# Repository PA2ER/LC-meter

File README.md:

# LC-meter
## Description
induction and capacity meter with pic controller.
*  Work in progress!!!
*  Finished version V1.0 of the PCB.
 
 Back side of the PCB.
 
 Front side of the PCB.
## Schematics
  
<!--stackedit_data:
eyJoaXN0b3J5IjpbLTg0MDYxMjgyM119
-->

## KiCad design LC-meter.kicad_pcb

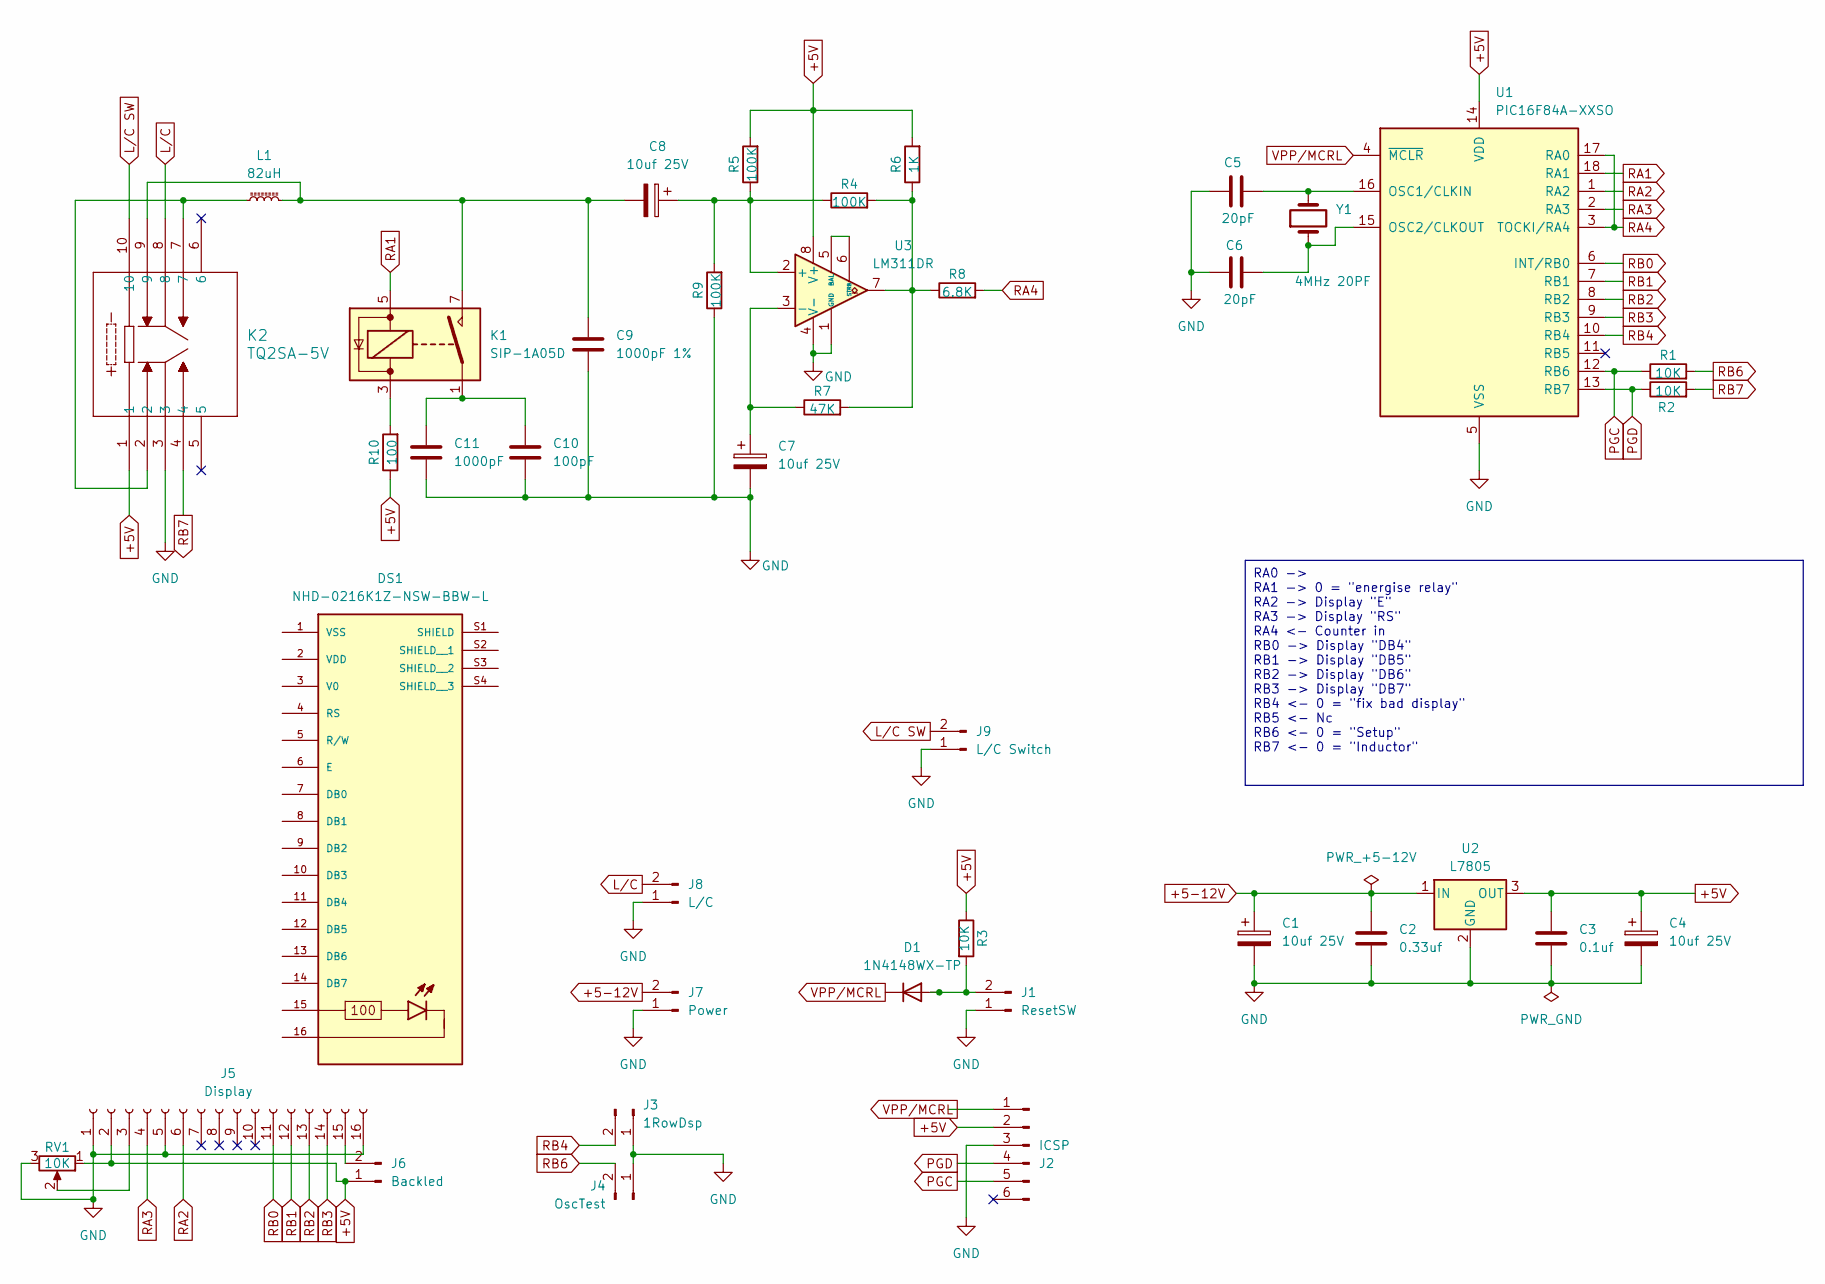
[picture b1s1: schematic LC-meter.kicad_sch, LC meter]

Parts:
C1, C4, C7, C8: 10uf 25V; CP_EIA-6032-28_Kemet-C_Pad2.25x2.35mm_HandSolder; Digikey 293D106X0025C2TE3
C2: 0.33uf; C_0805_2012Metric_Pad1.18x1.45mm_HandSolder; Digikey CC0805KKX7R8BB334
C3: 0.1uf; C_0805_2012Metric_Pad1.18x1.45mm_HandSolder; Digikey CC0805KRX7R9BB104
C5, C6: 20pF; C_0805_2012Metric_Pad1.18x1.45mm_HandSolder; Digikey C0805C200J5HAC7800
C9: 1000pF 1%; C_0805_2012Metric_Pad1.18x1.45mm_HandSolder; Digikey CC0805FRNPO9BN102
C10: 100pF; C_0805_2012Metric_Pad1.18x1.45mm_HandSolder; Digikey CC0805FRNPO9BN101
C11: 1000pF; C_0805_2012Metric_Pad1.18x1.45mm_HandSolder; Digikey CC0805FRNPO9BN102
D1: 1N4148WX-TP; D_SOD-323_HandSoldering; Digikey 1N4148WX-TP
DS1: NHD-0216K1Z-NSW-BBW-L; NHD_NHD-0216K1Z-NSW-BBW-L; PARTREV 03/28/17
J1: ResetSW; PinHeader_1x02_P2.54mm_Vertical
J2: ICSP; PinHeader_1x06_P2.54mm_Vertical
J3: 1RowDsp; PinHeader_1x02_P2.54mm_Vertical
J4: OscTest; PinHeader_1x02_P2.54mm_Vertical
J5: Display; PinHeader_1x16_P2.54mm_Vertical
J6: Backled; PinHeader_1x02_P2.54mm_Vertical
J7: Power; PinHeader_1x02_P2.54mm_Vertical
J8: L/C; PinHeader_1x02_P2.54mm_Vertical
J9: L/C Switch; PinHeader_1x02_P2.54mm_Vertical
K1: SIP-1A05D; Relay_SPST_StandexMeder_MS_Form1AB; Digikey SIP-1A05D
K2: TQ2SA-5V; RELAY_TQ2_SA_PAN-L
L1: 82uH; L_1210_3225Metric_Pad1.42x2.65mm_HandSolder; Digikey NLV32T-820J-EF
R1, R2, R3: 10K; R_0805_2012Metric_Pad1.20x1.40mm_HandSolder
R4, R5, R9: 100K; R_0805_2012Metric_Pad1.20x1.40mm_HandSolder
R6: 1K; R_0805_2012Metric_Pad1.20x1.40mm_HandSolder
R7: 47K; R_0805_2012Metric_Pad1.20x1.40mm_HandSolder
R8: 6.8K; R_0805_2012Metric_Pad1.20x1.40mm_HandSolder
R10: 100; R_0805_2012Metric_Pad1.20x1.40mm_HandSolder
RV1: 10K; Potentiometer_Bourns_TC33X_Vertical; Digikey TC33X-2-103E
U1: PIC16F84A-XXSO; SOIC-18W_7.5x11.6mm_P1.27mm; Digikey PIC16F84A-04/SO-ND
U2: L7805; TO-252-3_TabPin2; Digikey AS7805ADTR-G1DI
U3: LM311DR; SOIC-8_3.9x4.9mm_P1.27mm; Digikey IC COMPARATOR 1 GEN PUR 8SOIC
Y1: 4MHz 20PF; Crystal_SMD_HC49-SD_HandSoldering; Digikey 4M20P2/49SMT

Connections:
+5-12V: C1.1, C2.1, J7.2, U2.1 (IN)
+5V: C3.1, C4.1, J2.2, J5.2, J6.1, K2.1, R3.1, R5.2, R6.2, R10.1, RV1.1, U1.14 (VDD), U2.3 (OUT), U3.8 (V+)
GND: C1.2, C2.2, C3.2, C4.2, C5.1, C6.1, C7.2, C9.2, C10.2, C11.2, J1.1, J2.3, J3.1, J4.1, J5.1, J5.5, J5.16, J7.1, J8.1, J9.1, K2.3, R9.1, RV1.3, U1.5 (VSS), U2.2 (GND), U3.1 (GND), U3.4 (V-)
L/C: J8.2, K2.8
L/C SW: J9.2, K2.10
unnamed: C8.2, C9.1, K1.7, K2.9, L1.2
unnamed: C10.1, C11.1, K1.1
unnamed: D1.2 (A), J1.2, R3.2
unnamed: J5.3, RV1.2
unnamed: J5.15, J6.2
unnamed: K1.3, R10.2
unnamed: K2.2, K2.7, L1.1
unnamed: R4.2, R6.1, R7.2, R8.1, U3.7
unnamed: C5.2, U1.16 (OSC1/CLKIN), Y1.2
unnamed: C6.2, U1.15 (OSC2/CLKOUT), Y1.1
unnamed: C8.1, R4.1, R5.1, R9.2, U3.2 (+)
unnamed: C7.1, R7.1, U3.3 (-)
unnamed: U3.5 (BAL), U3.6 (STRB)
PGC: J2.5, R1.1, U1.12 (RB6)
PGD: J2.4, R2.1, U1.13 (RB7)
RA1: K1.5, U1.18 (RA1)
RA2: J5.6, U1.1 (RA2)
RA3: J5.4, U1.2 (RA3)
RA4: R8.2, U1.3 (TOCKI/RA4), U1.17 (RA0)
RB0: J5.11, U1.6 (INT/RB0)
RB1: J5.12, U1.7 (RB1)
RB2: J5.13, U1.8 (RB2)
RB3: J5.14, U1.9 (RB3)
RB4: J3.2, U1.10 (RB4)
RB6: J4.2, R1.2
RB7: K2.4, R2.2
VPP/MCRL: D1.1 (K), J2.1, U1.4 (~MCLR)

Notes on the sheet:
RA0 -> RA1 -> 0 = "energise relay" RA2 -> Display "E" RA3 -> Display "RS" RA4 <- Counter in RB0 -> Display "DB4" RB1 -> Display "DB5" RB2 -> Display "DB6" RB3 -> Display "DB7" RB4 <- 0 = "fix bad display" RB5 <- Nc RB6 <- 0 = "Setup" RB7 <- 0 = "Inductor"

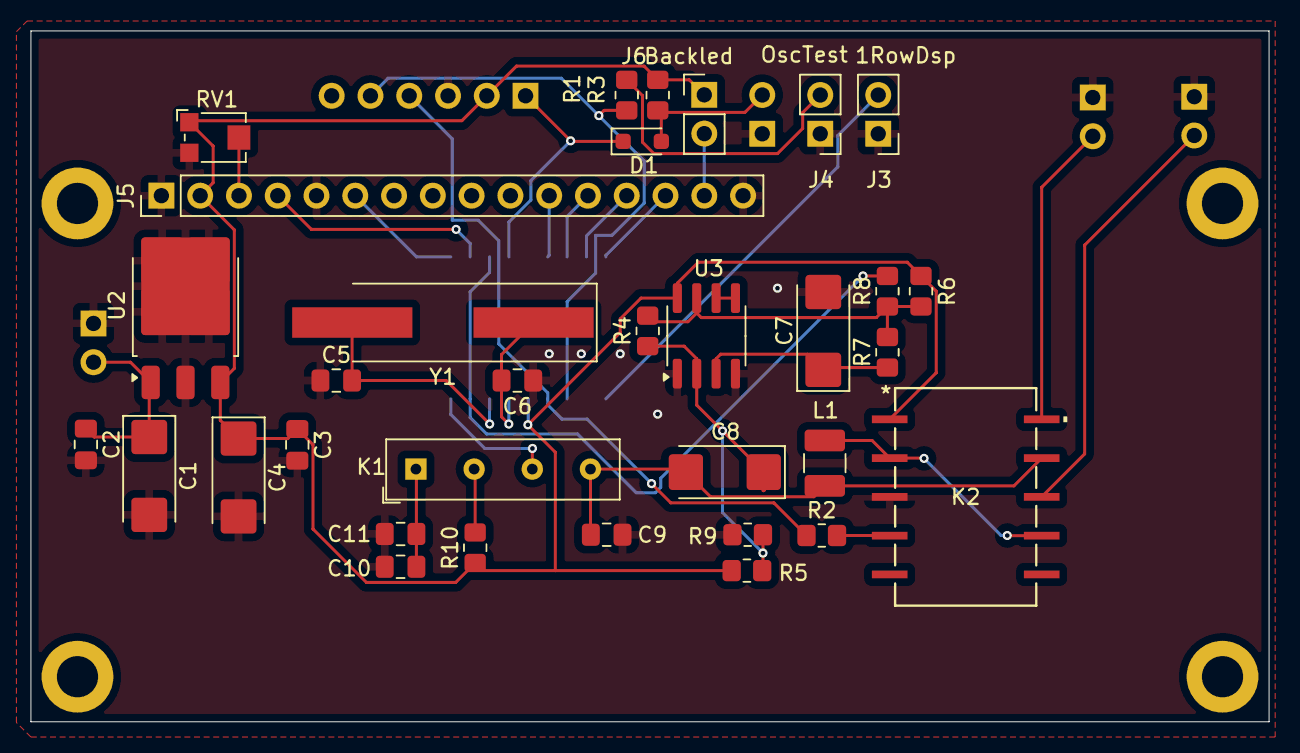
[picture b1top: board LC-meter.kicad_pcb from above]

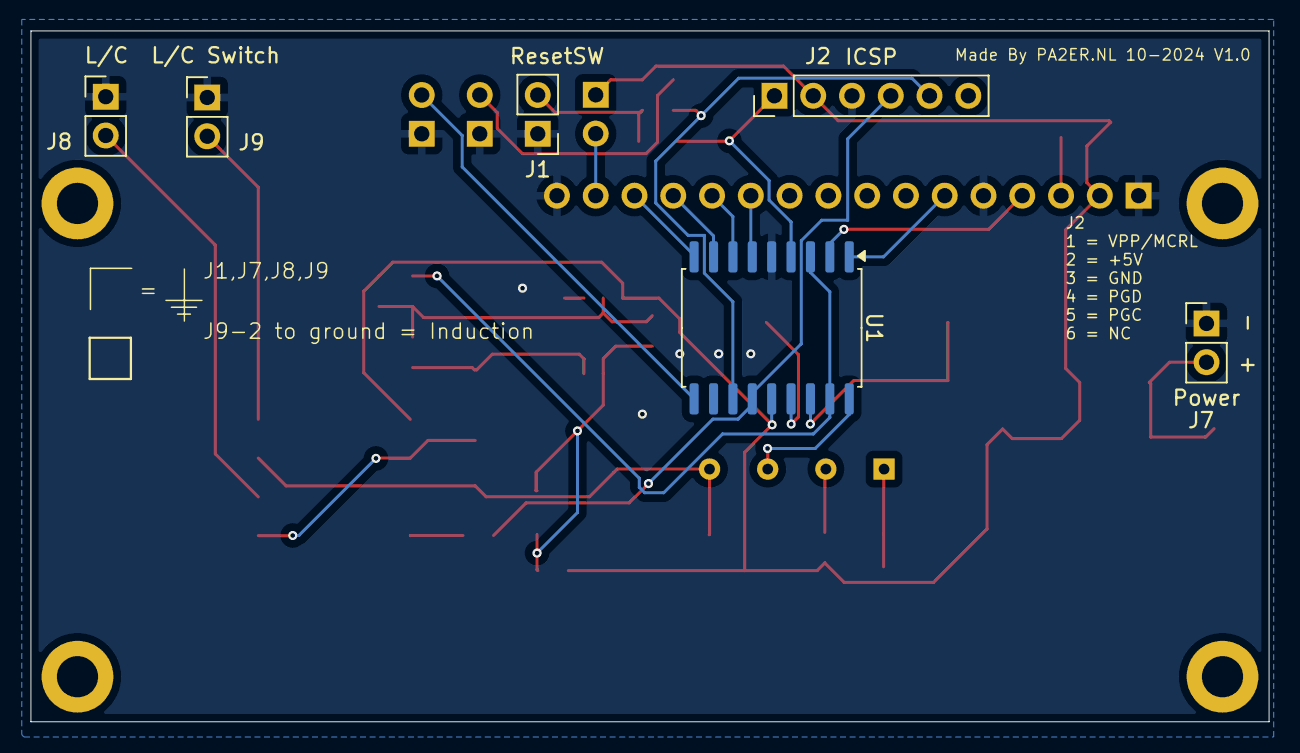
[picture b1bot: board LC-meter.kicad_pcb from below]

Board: 2 copper layers, 81.1 x 45.2 mm, 39 parts (6 on the bottom side), 32 nets.

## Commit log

2024-10-07 add *.lck to gitignore
2024-10-09 9-10-2024
2024-10-09 add display
2024-10-11 11-10-2024
2024-10-11 11-10-2024 PCB ready
2024-10-11 add pictures
2024-10-12 README.md updated from https://stackedit.io/
2024-10-12 README.md.md created from https://stackedit.io/
2024-10-12 readme update
2024-10-27 Update 23-10-2024
